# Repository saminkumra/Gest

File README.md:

# CE347_Gest
###### By Joshua Feist, Isabelle Johnson, Samin Kumra, Seth May, Haroon Nawaz, Danche Smilkova, and Chris Uustal

### What is Gest? 
The next generation of human-computer interface devices. 

### How does it work? 
While wearing a Gest, you can connect to your laptop and perform different gestures
which then map to basic functions on your computer. 

### Is it open source? 
Yes! That's why all the code is on GitHub. 

### Update Log:
- Added BLE connectivity
	- Requires ESP32 or similar BLE-enabled microcontroller
- Added basic mouse movement support
	- Requires BNO055 sensor

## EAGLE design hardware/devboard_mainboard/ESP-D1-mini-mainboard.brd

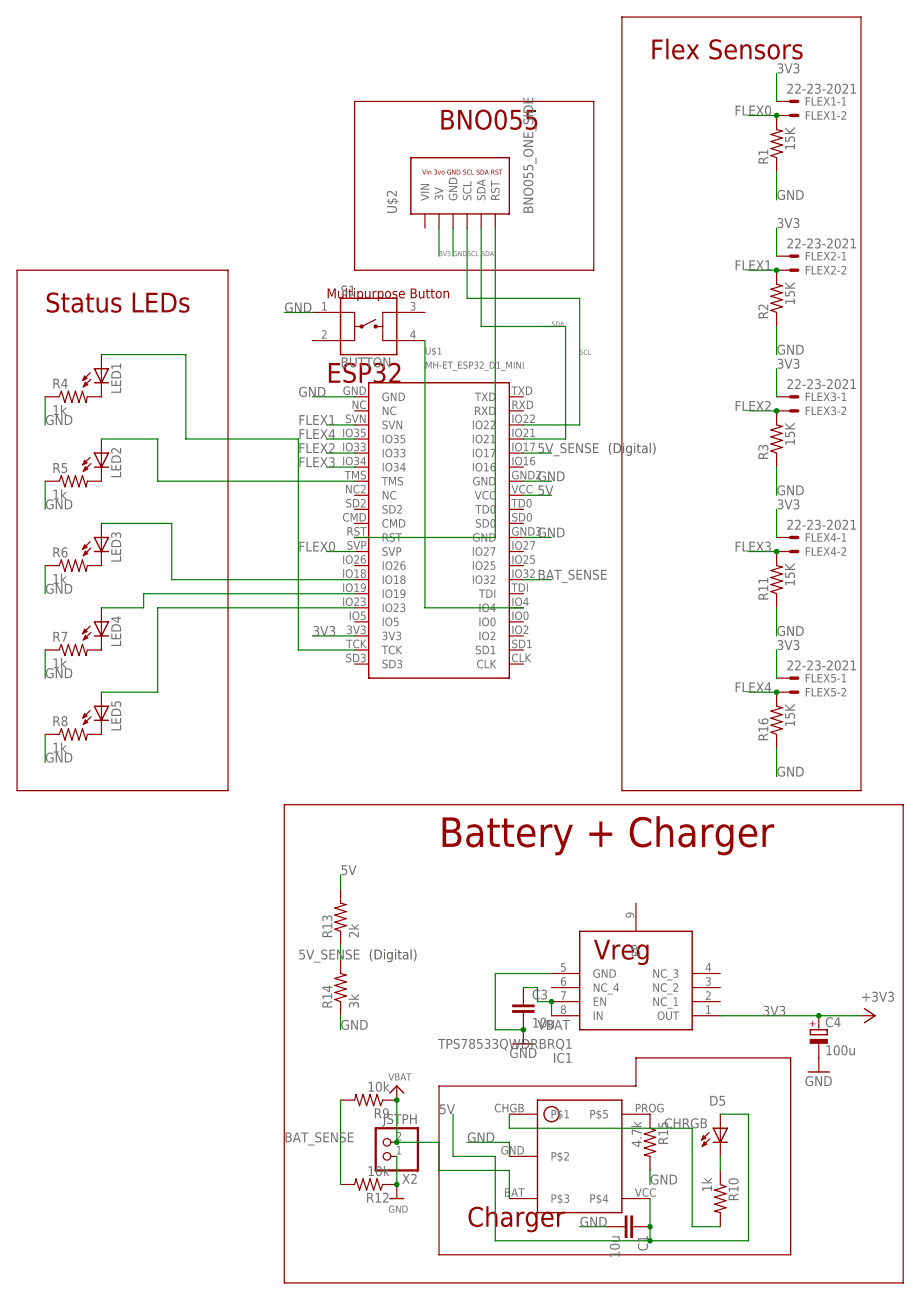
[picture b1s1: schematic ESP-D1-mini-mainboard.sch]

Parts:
C1, C3: 10u; C0805
C4: 100u; B/3528-21W
D5: GREEN; CHIPLED_0805
FLEX1, FLEX2, FLEX3, FLEX4, FLEX5: 22-23-2021
IC1: TPS78533QWDRBRQ1; SON65P300X300X100-9N
LED1, LED2, LED3, LED4, LED5: LEDCHIPLED_0805; CHIPLED_0805
R1, R2, R3, R11, R16: 15K; M0805
R4, R5, R6, R7, R8, R10: 1k; M0805
R9, R12: 10k; M0805
R13: 2k; M0805
R14: 3k; M0805
R15: 4.7k; M0805
S1: BUTTON; BUTTON_4_PAD
U1: DIO5518BAUK+; SOT23-5L
U$1: MH-ET_ESP32_D1_MINI
U$2: BNO055_ONE_SIDE
X2: JSTPH; JSTPH2

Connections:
3V3: C4.+, FLEX1.1, FLEX2.1, FLEX3.1, FLEX4.1, FLEX5.1, IC1.1 (OUT), U$1.3V3, U$2.3V
5V: C1.1, D5.A, R13.2, U1.VCC, U$1.VCC
5V_SENSE: R13.1, R14.2, U$1.IO17
BAT_SENSE: R9.2, R12.2, U$1.IO32
CHRGB: R10.2, U1.CHGB
FLEX0: FLEX1.2, R1.2, U$1.SVP
FLEX1: FLEX2.2, R2.2, U$1.SVN
FLEX2: FLEX3.2, R3.2, U$1.IO33
FLEX3: FLEX4.2, R11.2, U$1.IO34
FLEX4: FLEX5.2, R16.2, U$1.IO35
GND: C1.2, C3.2, C4.-, IC1.5 (GND), R1.1, R2.1, R3.1, R4.1, R5.1, R6.1, R7.1, R8.1, R11.1, R12.1, R14.1, R15.2, R16.1, S1.1, U1.GND, U$1.GND, U$1.GND2 (GND), U$1.GND3 (GND), U$2.GND, X2.1
unnamed: LED1.C, R4.2
unnamed: LED2.C, R5.2
unnamed: LED3.C, R6.2
unnamed: LED4.C, R7.2
unnamed: LED5.C, R8.2
unnamed: LED1.A, U$1.TCK
unnamed: LED2.A, U$1.TMS
unnamed: S1.4, U$1.IO4
unnamed: LED3.A, U$1.IO18
unnamed: U$1.RST, U$2.RST
unnamed: D5.C, R10.1
unnamed: LED4.A, U$1.IO19
unnamed: LED5.A, U$1.IO23
PROG: R15.1, U1.PROG
SCL: U$1.IO22, U$2.SCL
SDA: U$1.IO21, U$2.SDA
VBAT: C3.1, IC1.7 (EN), IC1.8 (IN), R9.1, U1.BAT, X2.2

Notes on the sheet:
BNO055
Vin 3vo GND SCL SDA RST
Flex Sensors
Multipurpose Button
Charger
ESP32
Vreg
Battery + Charger
Status LEDs
(Digital)

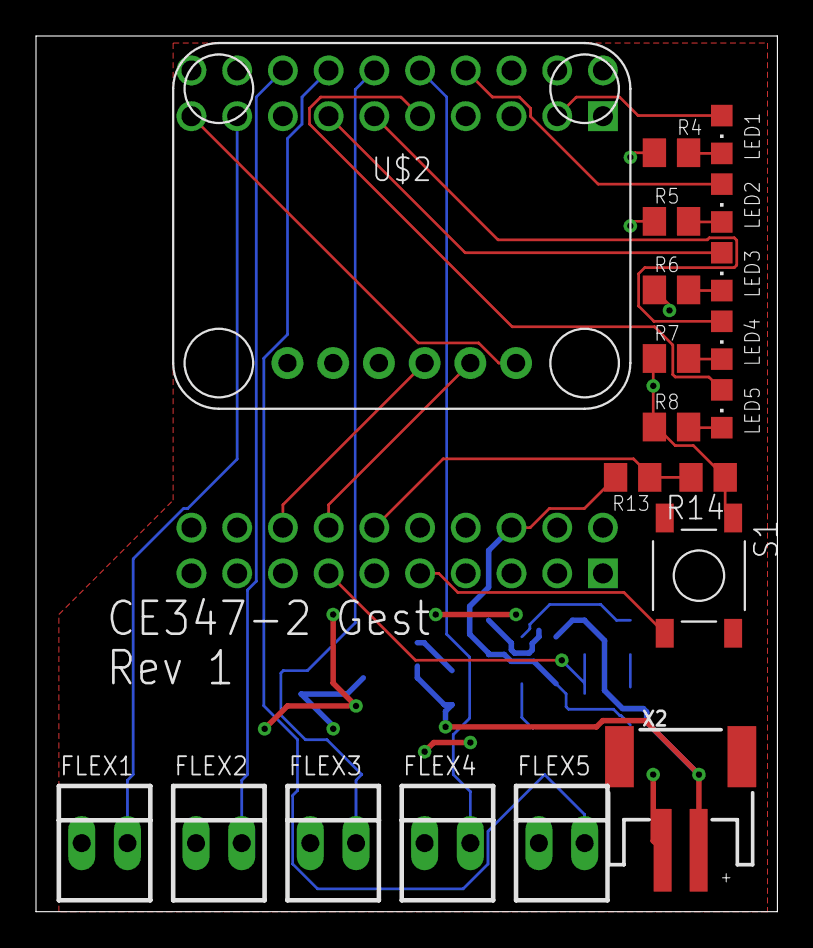
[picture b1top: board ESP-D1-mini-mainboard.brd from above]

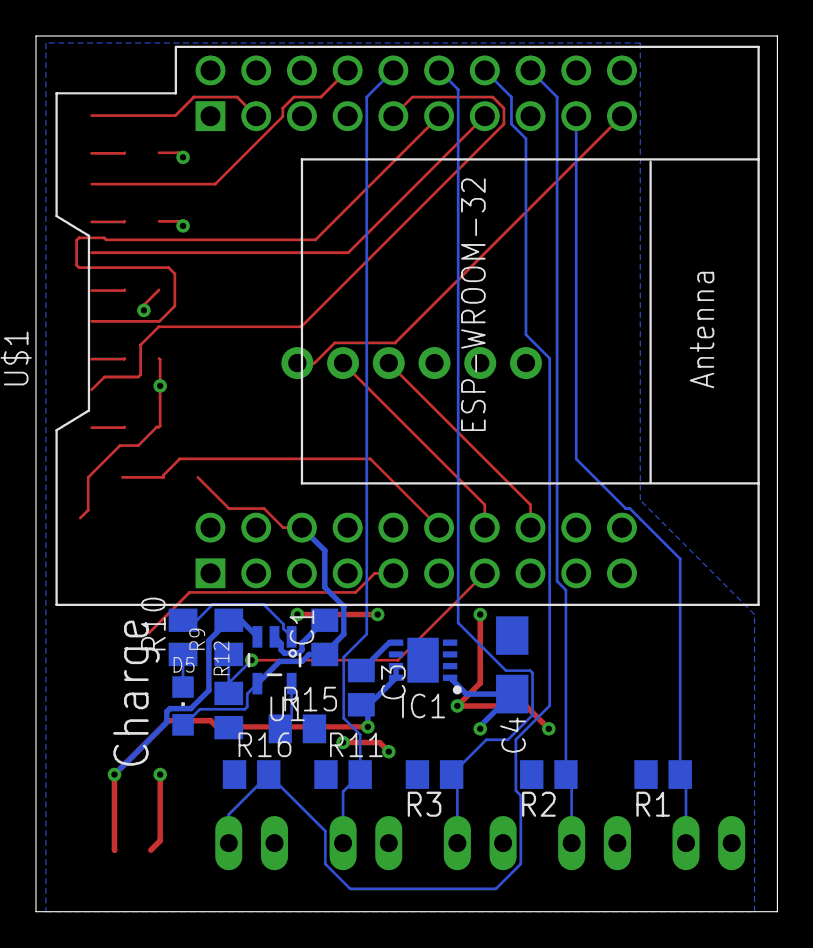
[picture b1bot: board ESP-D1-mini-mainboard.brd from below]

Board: 2 copper layers, 41.2 x 48.6 mm, 36 parts (16 on the bottom side), 28 nets.

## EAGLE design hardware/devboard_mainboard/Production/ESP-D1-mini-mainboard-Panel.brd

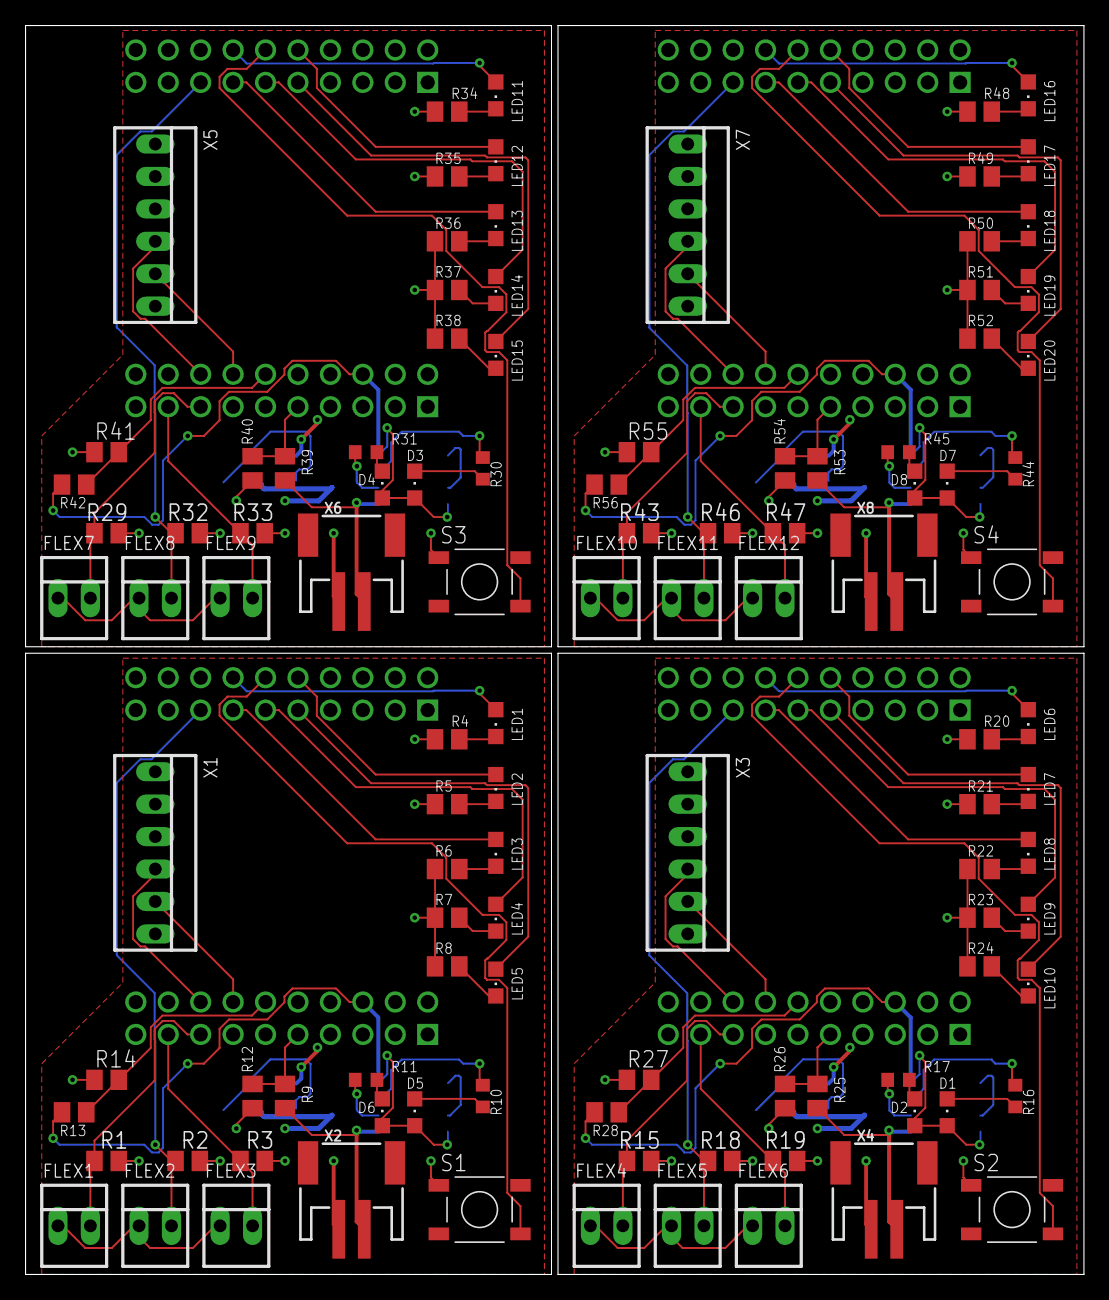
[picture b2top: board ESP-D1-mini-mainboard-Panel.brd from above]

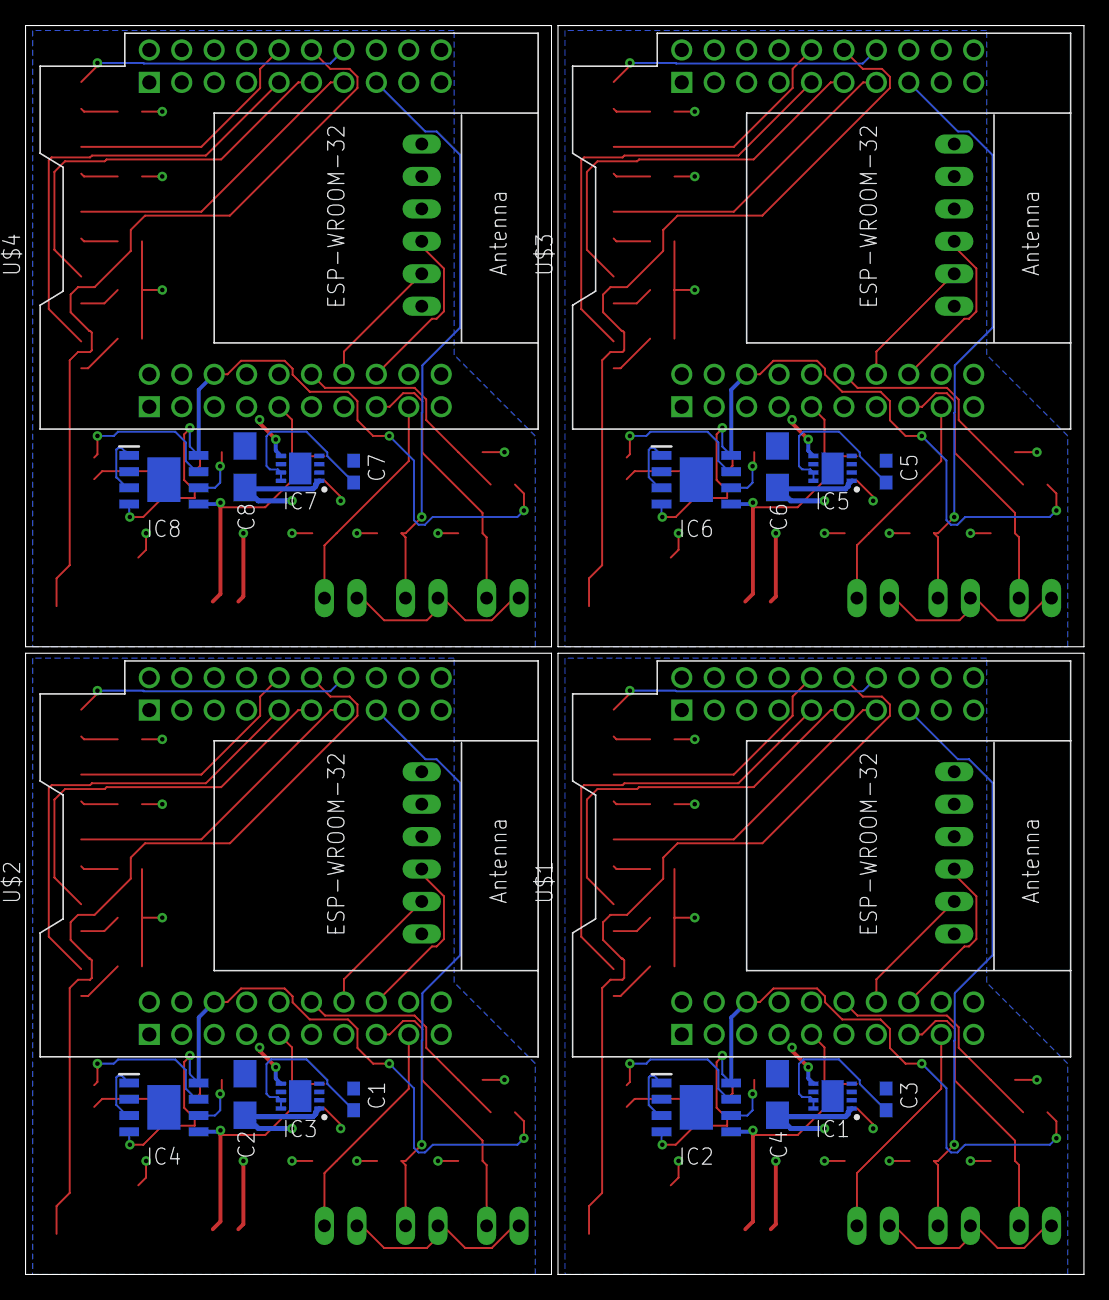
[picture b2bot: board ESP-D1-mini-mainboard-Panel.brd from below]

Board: 2 copper layers, 82.9 x 97.8 mm, 128 parts (20 on the bottom side), 116 nets.

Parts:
C1, C3, C5, C7: 10u; C0603
C2, C4, C6, C8: 100u; B/3528-21W
D1, D2, D3, D4, D5, D6, D7, D8: GREEN; CHIPLED_0805
FLEX1, FLEX2, FLEX3, FLEX4, FLEX5, FLEX6, FLEX7, FLEX8, FLEX9, FLEX10, FLEX11, FLEX12: 22-23-2021
IC1, IC3, IC5, IC7: TPS78533QWDRBRQ1; SON65P300X300X100-9N
IC2, IC4, IC6, IC8: DIO5508XS8; SOIC127P600X170-9N
LED1, LED2, LED3, LED4, LED5, LED6, LED7, LED8, LED9, LED10, LED11, LED12, LED13, LED14, LED15, LED16, LED17, LED18, LED19, LED20: CHIPLED_0805
R1, R2, R3, R15, R18, R19, R29, R32, R33, R43, R46, R47: 15K; M0805
R4, R5, R6, R7, R8, R20, R21, R22, R23, R24, R34, R35, R36, R37, R38, R48, R49, R50, R51, R52: 1k; M0805
R9, R12, R25, R26, R39, R40, R53, R54: 10k; M0805
R10, R11, R16, R17, R30, R31, R44, R45: 470; R0603
R13, R28, R42, R56: 2k; M0805
R14, R27, R41, R55: 3k; M0805
S1, S2, S3, S4: BUTTON; BUTTON_4_PAD
U$1, U$2, U$3, U$4: MH-ET_ESP32_D1_MINI
X1, X3, X5, X7: 22-23-2061
X2, X4, X6, X8: JSTPH; JSTPH2

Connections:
3V1: FLEX4.1, FLEX5.1, FLEX6.1, U$2.3V3, X3.2
3V2: FLEX7.1, FLEX8.1, FLEX9.1, U$3.3V3, X5.2
3V3: FLEX1.1, FLEX2.1, FLEX3.1, U$1.3V3, X1.2
3V4: FLEX10.1, FLEX11.1, FLEX12.1, U$4.3V3, X7.2
5V: D5.A, D6.A, IC2.4, IC2.8, R13.2, U$1.VCC
5V1: D1.A, D2.A, IC4.4, IC4.8, R28.2, U$2.VCC
5V2: D3.A, D4.A, IC6.4, IC6.8, R42.2, U$3.VCC
5V3: D7.A, D8.A, IC8.4, IC8.8, R56.2, U$4.VCC
5V_SENSE: R13.1, R14.2, U$1.IO17
5V_SENSE1: R27.2, R28.1, U$2.IO17
5V_SENSE2: R41.2, R42.1, U$3.IO17
5V_SENSE3: R55.2, R56.1, U$4.IO17
+3V1: C2.+, IC3.1
+3V2: C6.+, IC5.1
+3V3: C4.+, IC1.1
+3V4: C8.+, IC7.1
BAT_SENSE: R9.2, R12.2, U$1.IO4
BAT_SENSE1: R25.2, R26.2, U$2.IO4
BAT_SENSE2: R39.2, R40.2, U$3.IO4
BAT_SENSE3: R53.2, R54.2, U$4.IO4
GND: C3.2, C4.-, IC1.5, R1.1, R2.1, R3.1, R4.1, R5.1, R6.1, R7.1, R8.1, R12.1, R14.1, S1.1, U$1.GND, U$1.GND2, X1.3, X2.1
GND1: C1.2, C2.-, IC3.5, R15.1, R18.1, R19.1, R20.1, R21.1, R22.1, R23.1, R24.1, R26.1, R27.1, S2.1, U$2.GND, U$2.GND2, X3.3, X4.1
GND2: C5.2, C6.-, IC5.5, R29.1, R32.1, R33.1, R34.1, R35.1, R36.1, R37.1, R38.1, R40.1, R41.1, S3.1, U$3.GND, U$3.GND2, X5.3, X6.1
GND3: C7.2, C8.-, IC7.5, R43.1, R46.1, R47.1, R48.1, R49.1, R50.1, R51.1, R52.1, R54.1, R55.1, S4.1, U$4.GND, U$4.GND2, X7.3, X8.1
unnamed: LED1.C, R4.2
unnamed: LED2.C, R5.2
unnamed: LED3.C, R6.2
unnamed: LED4.C, R7.2
unnamed: LED5.C, R8.2
unnamed: FLEX1.2, R1.2, U$1.IO25
unnamed: FLEX2.2, R2.2, U$1.IO26
unnamed: FLEX3.2, R3.2, U$1.IO27
unnamed: LED1.A, U$1.IO35
unnamed: LED2.A, U$1.IO34
unnamed: S1.4, U$1.IO33
unnamed: LED3.A, U$1.IO18
unnamed: IC2.1, IC2.3
unnamed: D5.C, R10.2
unnamed: D6.C, R11.2
unnamed: IC2.7, R10.1
unnamed: IC2.6, R11.1
unnamed: C3.1, IC1.7, IC1.8
unnamed: LED4.A, U$1.IO19
unnamed: LED5.A, U$1.IO23
unnamed: FLEX4.2, R15.2, U$2.IO25
unnamed: FLEX5.2, R18.2, U$2.IO26
unnamed: FLEX6.2, R19.2, U$2.IO27
unnamed: S2.4, U$2.IO33
unnamed: IC4.1, IC4.3
unnamed: D1.C, R16.2
unnamed: D2.C, R17.2
unnamed: IC4.7, R16.1
unnamed: IC4.6, R17.1
unnamed: C1.1, IC3.7, IC3.8
unnamed: LED6.C, R20.2
unnamed: LED7.C, R21.2
unnamed: LED8.C, R22.2
unnamed: LED9.C, R23.2
unnamed: LED10.C, R24.2
unnamed: LED6.A, U$2.IO35
unnamed: LED7.A, U$2.IO34
unnamed: LED8.A, U$2.IO18
unnamed: LED9.A, U$2.IO19
unnamed: LED10.A, U$2.IO23
unnamed: FLEX7.2, R29.2, U$3.IO25
unnamed: FLEX8.2, R32.2, U$3.IO26
unnamed: FLEX9.2, R33.2, U$3.IO27
unnamed: S3.4, U$3.IO33
unnamed: IC6.1, IC6.3
unnamed: D3.C, R30.2
unnamed: D4.C, R31.2
unnamed: IC6.7, R30.1
unnamed: IC6.6, R31.1
unnamed: C5.1, IC5.7, IC5.8
unnamed: LED11.C, R34.2
unnamed: LED12.C, R35.2
unnamed: LED13.C, R36.2
unnamed: LED14.C, R37.2
unnamed: LED15.C, R38.2
unnamed: LED11.A, U$3.IO35
unnamed: LED12.A, U$3.IO34
unnamed: LED13.A, U$3.IO18
unnamed: LED14.A, U$3.IO19
unnamed: LED15.A, U$3.IO23
unnamed: FLEX10.2, R43.2, U$4.IO25
unnamed: FLEX11.2, R46.2, U$4.IO26
unnamed: FLEX12.2, R47.2, U$4.IO27
unnamed: S4.4, U$4.IO33
unnamed: IC8.1, IC8.3
unnamed: D7.C, R44.2
unnamed: D8.C, R45.2
unnamed: IC8.7, R44.1
unnamed: IC8.6, R45.1
unnamed: C7.1, IC7.7, IC7.8
unnamed: LED16.C, R48.2
unnamed: LED17.C, R49.2
unnamed: LED18.C, R50.2
unnamed: LED19.C, R51.2
unnamed: LED20.C, R52.2
unnamed: LED16.A, U$4.IO35
unnamed: LED17.A, U$4.IO34
unnamed: LED18.A, U$4.IO18
unnamed: LED19.A, U$4.IO19
unnamed: LED20.A, U$4.IO23
SCL: U$1.IO22, X1.4
SCL1: U$2.IO22, X3.4
SCL2: U$3.IO22, X5.4
SCL3: U$4.IO22, X7.4
SDA: U$1.IO21, X1.5
SDA1: U$2.IO21, X3.5
SDA2: U$3.IO21, X5.5
SDA3: U$4.IO21, X7.5
VBAT: IC2.5, R9.1, X2.2
VBAT1: IC4.5, R25.1, X4.2
VBAT2: IC6.5, R39.1, X6.2
VBAT3: IC8.5, R53.1, X8.2

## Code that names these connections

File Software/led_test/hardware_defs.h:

//hardware_defs.h

//#define REV0
#define REV1

/*
 * All the hardware related #define are placed within here
 */

#ifndef HARDWARE_DEFS_H
#define HARDWARE_DEFS_H

#ifdef REV0

#define FLEX1 25
#define FLEX2 26
#define FLEX3 27

#define BUTTON 33

#define LED1 13
#define LED2 14
#define LED3 18
#define LED4 19
#define LED5 23

#define BAT_SENSE 4
#define BAT_RATIO 2
#define VBUS_SENSE 17

#define FLEX_PULLDOWN 15 //no longer INPUT_PULLDOWN due to issues//tested to be 17.25+-0.25 kohms

#endif

#ifdef REV1

#define LED1 13
#define LED2 14
#define LED3 18
#define LED4 19
#define LED5 23

#define FLEX0 36
#define FLEX1 39
#define FLEX2 33
#define FLEX3 34
#define FLEX4 35

#define BUTTON 4

#define BAT_SENSE 32
#define BAT_RATIO 2
#define VBUS_SENSE 17 //digital

#define FLEX_PULLDOWN 15

#endif

#endif 

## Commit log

2022-08-04 new repo

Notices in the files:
parts and their libraries:
microbuilder: This work is placed in the public domain, and may be freely used for commercial and non-commercial work with the following conditions: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
